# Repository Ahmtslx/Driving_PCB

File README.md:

# Driving_PCB
This repository is made to share my driving pcb schematics and footprints. It mainly uses kicad and my(and my teammates's) work will be displayed here.

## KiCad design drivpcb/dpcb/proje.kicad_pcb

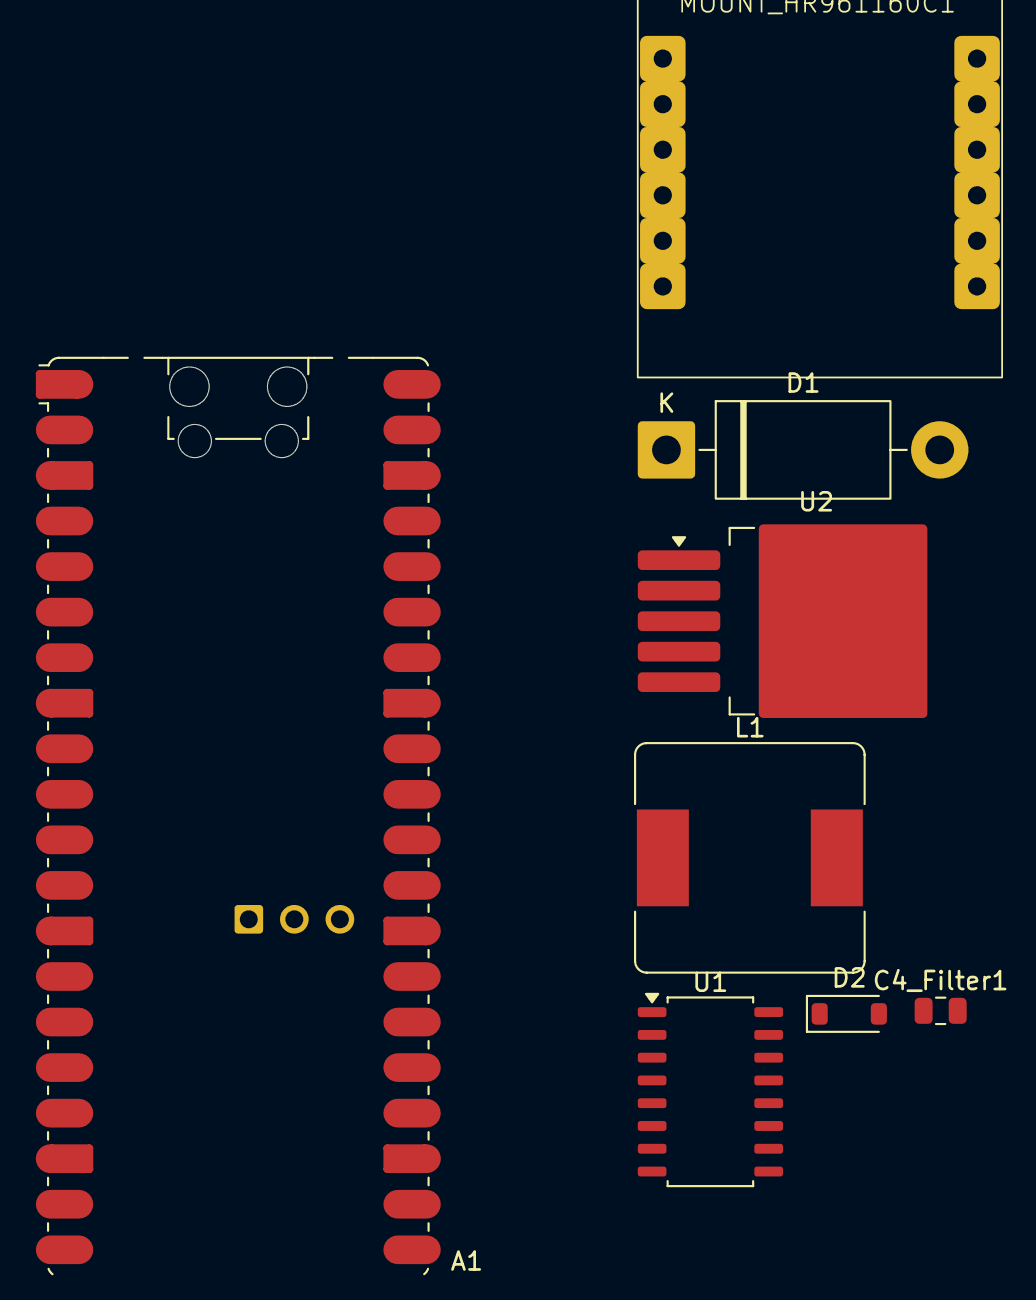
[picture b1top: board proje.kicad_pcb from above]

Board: 2 copper layers, 8 parts (0 on the bottom side), 10 nets, no tracks yet.

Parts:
A1: RaspberryPi_Pico_W; RaspberryPi_Pico_W_SMD_HandSolder
C4_Filter1: 100nF; C_0805_2012Metric
D1: D_Schottky; D_DO-201AD_P15.24mm_Horizontal
D2: 1N4148W; D_SOD-123
L1: 33uH; L_Bourns_SRR1260
MOUNT_HR961160C1: U1; EthernetMount
U1: TLP291-4; SOIC-16_4.55x10.3mm_P1.27mm
U2: LM2596S-3.3; TO-263-5_TabPin3

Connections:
+3.3V: A1.36 (3V3), MOUNT_HR961160C1.8 (+3V3), MOUNT_HR961160C1.9 (+3V3)
GND: A1.3 (GND), A1.8 (GND), A1.13 (GND), A1.18 (GND), A1.23 (GND), A1.28 (GND), A1.38 (GND), D1.1 (K), MOUNT_HR961160C1.1 (GND), MOUNT_HR961160C1.2 (GND), MOUNT_HR961160C1.7 (GND), U1.8, U1.9, U2.3 (GND), U2.4 (FB), U2.5 (~ON/OFF)
unnamed: A1.21 (GPIO16), MOUNT_HR961160C1.12 (MISO)
unnamed: A1.22 (GPIO17), MOUNT_HR961160C1.5 (CS)
unnamed: A1.24 (GPIO18), MOUNT_HR961160C1.4 (SCK)
unnamed: A1.25 (GPIO19), MOUNT_HR961160C1.3 (MOSI)
unnamed: A1.39 (VSYS), A1.40 (VBUS), L1.2
unnamed: D1.2 (A), L1.1, U2.2 (OUT)
unnamed: C4_Filter1.2, D2.2 (A), U1.10
unnamed: C4_Filter1.1, D2.1 (K)

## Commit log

2025-12-23 Add disregard file
